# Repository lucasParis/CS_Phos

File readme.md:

Phos
===

USB Serial Protocol for Led Controllers
---
There is one led controller per side of the led pilar.
Each controller is being streamed frames 60 times a second of the leds' brightness by USB serial.
The protocol for the serial transmition consists of a __start byte of 255__ followed by a __list of 3564 bytes of brightness values between 0 and 254__.
These brightness values correspond to each pixel of the strip in series. The strips are arranged in 9 colomns, each with 11 modules of 36pixels long -i.e. 396 leds per colomn.
The data is listed one colomn after the other, starting and the top of the left colomn and making it's way down and then to the next colomn.
Serial baud is 2500000.

Arduino
---
- FastLED version 3.1.6
- Arduino 1.8.2
- Teensyloader 1.26

The best settings to avoid glitches in the apa102 data seems to be:
- teensy clock speed set to 144mhz
- fastled rate 3mhz

Serial baud is 2500000.

The _testCode_ firmware of prototype 2 loops 2 white leds through the strip.

Assembly
---
ribbon cables
power

TouchDesigner patch
---
### prototype 1
Test patch with internally generated patterns and UI to adjust patterns
### prototype 2
streaming patch, with syphon/spout input (to do).
- [ ] add syphon/spout input
- [ ] cleanup UI
- [ ] adapt test patterns from prototype 1
- [ ] add processing example code
- [ ] change total output for only 3 boxes, 1 side

Files
---
- prototype 1
  - Made in september 2018 for tests at the barbican
  - 1 box, 5 strips
- prototype 2
  - Made in October/November 2018
  - 3 boxes, 9 strips, 2 sides
  - custom pcbs version 1, with small changes needed
  - digikey BOMs

BOMs
---

#### BOM_leds_oneBoxSide_digikey

Bill of materials for 1 side of the box, includes power supply and connectors for 6 led breakout pcbs.
2 needed per box.

####  BOM_masterModule_digikey

Bill of materials for master module

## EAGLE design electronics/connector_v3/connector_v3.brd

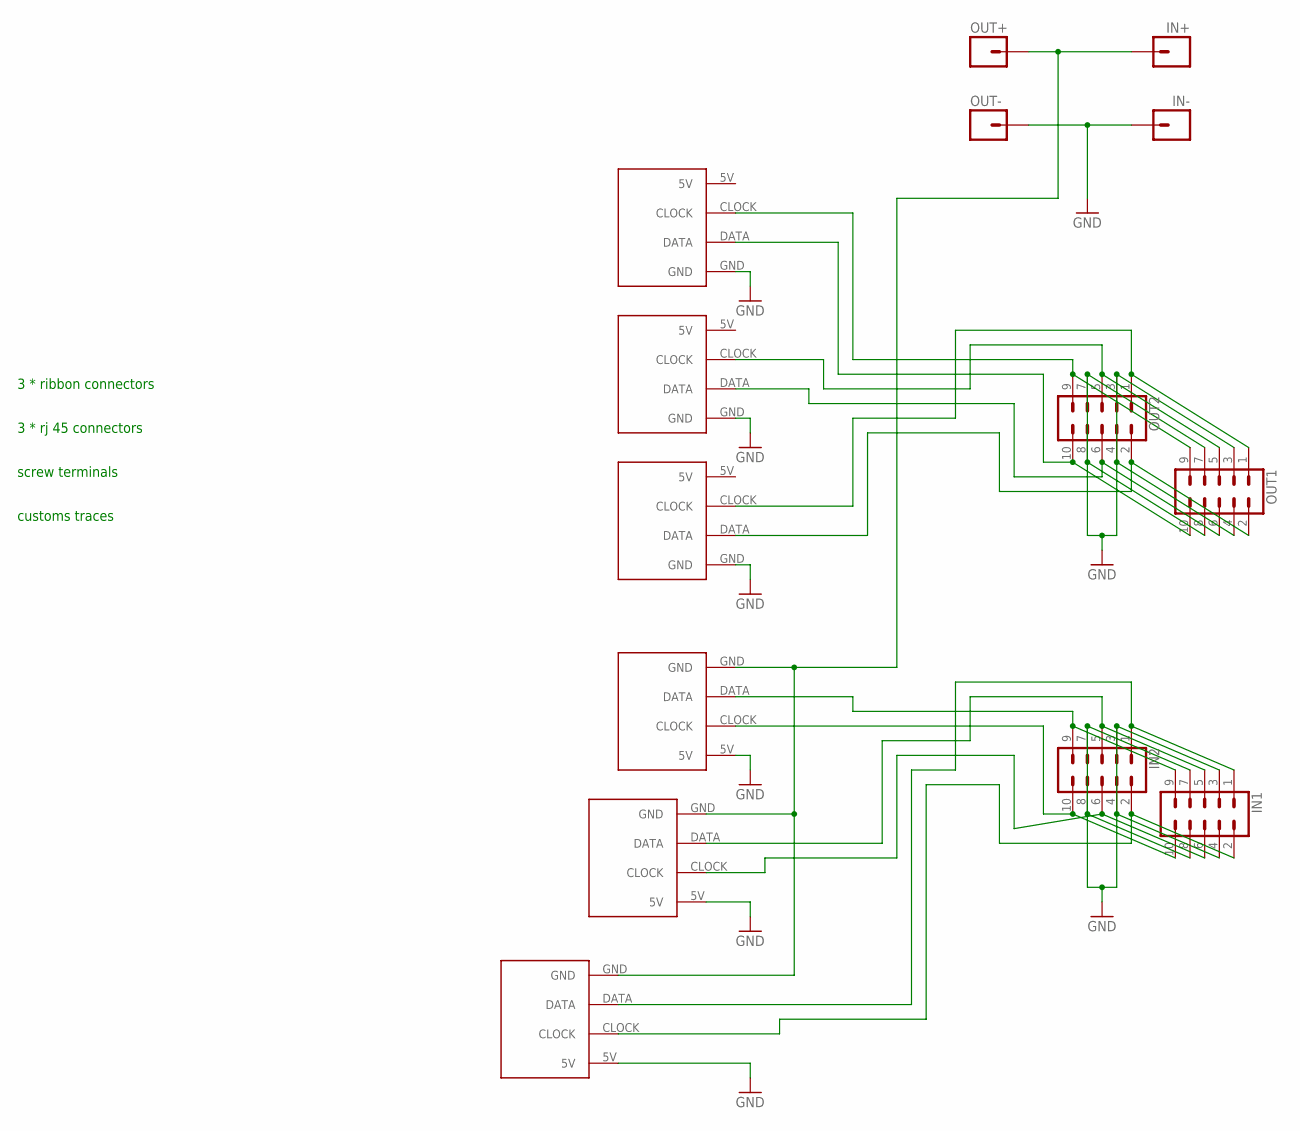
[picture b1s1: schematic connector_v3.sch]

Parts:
IN1, IN2: CONN_05X2SHD_LOCK; 2X5-SHROUDED_LOCK
IN+: M01PTH_2MM; 1X01_2MM
IN-: M01PTH_2MM; 1X01_2MM
INSTRIP1, INSTRIP2, INSTRIP3: APA102STRIP
OUT1, OUT2: CONN_05X2SHD_LOCK; 2X5-SHROUDED_LOCK
OUT+: M01PTH_2MM; 1X01_2MM
OUT-: M01PTH_2MM; 1X01_2MM
OUTSTRIP1, OUTSTRIP2, OUTSTRIP3: APA102STRIP

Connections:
GND: IN1.3, IN1.4, IN1.7, IN1.8, IN2.3, IN2.4, IN2.7, IN2.8, IN-.1, INSTRIP1.5V, INSTRIP2.5V, INSTRIP3.5V, OUT1.3, OUT1.4, OUT1.7, OUT1.8, OUT2.3, OUT2.4, OUT2.7, OUT2.8, OUT-.1, OUTSTRIP1.GND, OUTSTRIP2.GND, OUTSTRIP3.GND
unnamed: IN1.9, IN2.9, INSTRIP3.DATA
unnamed: IN1.10, IN2.10, INSTRIP3.CLOCK
unnamed: IN1.5, IN2.5, INSTRIP2.DATA
unnamed: IN1.6, IN2.6, INSTRIP2.CLOCK
unnamed: IN1.1, IN2.1, INSTRIP1.DATA
unnamed: IN1.2, IN2.2, INSTRIP1.CLOCK
unnamed: IN+.1, INSTRIP1.GND, INSTRIP2.GND, INSTRIP3.GND, OUT+.1
unnamed: OUT1.9, OUT2.9, OUTSTRIP3.CLOCK
unnamed: OUT1.10, OUT2.10, OUTSTRIP3.DATA
unnamed: OUT1.5, OUT2.5, OUTSTRIP2.CLOCK
unnamed: OUT1.6, OUT2.6, OUTSTRIP2.DATA
unnamed: OUT1.1, OUT2.1, OUTSTRIP1.CLOCK
unnamed: OUT1.2, OUT2.2, OUTSTRIP1.DATA

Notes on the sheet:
3 * rj 45 connectors
3 * ribbon connectors
screw terminals
customs traces

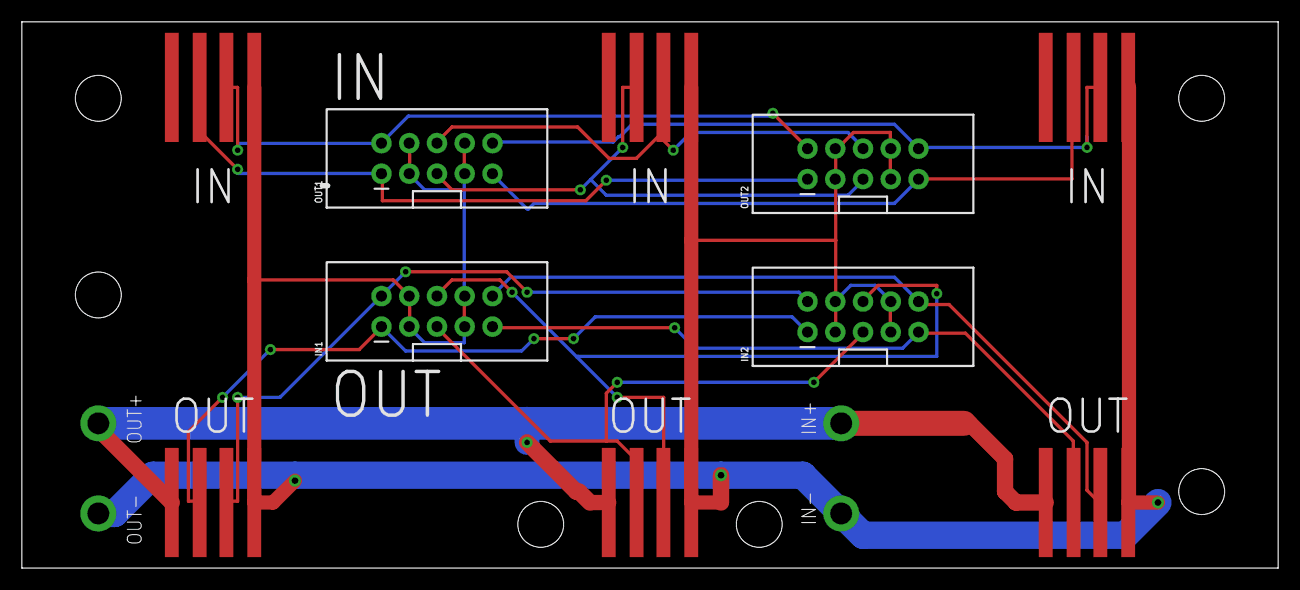
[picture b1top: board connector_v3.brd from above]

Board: 2 copper layers, 115.0 x 50.0 mm, 14 parts (0 on the bottom side), 14 nets.

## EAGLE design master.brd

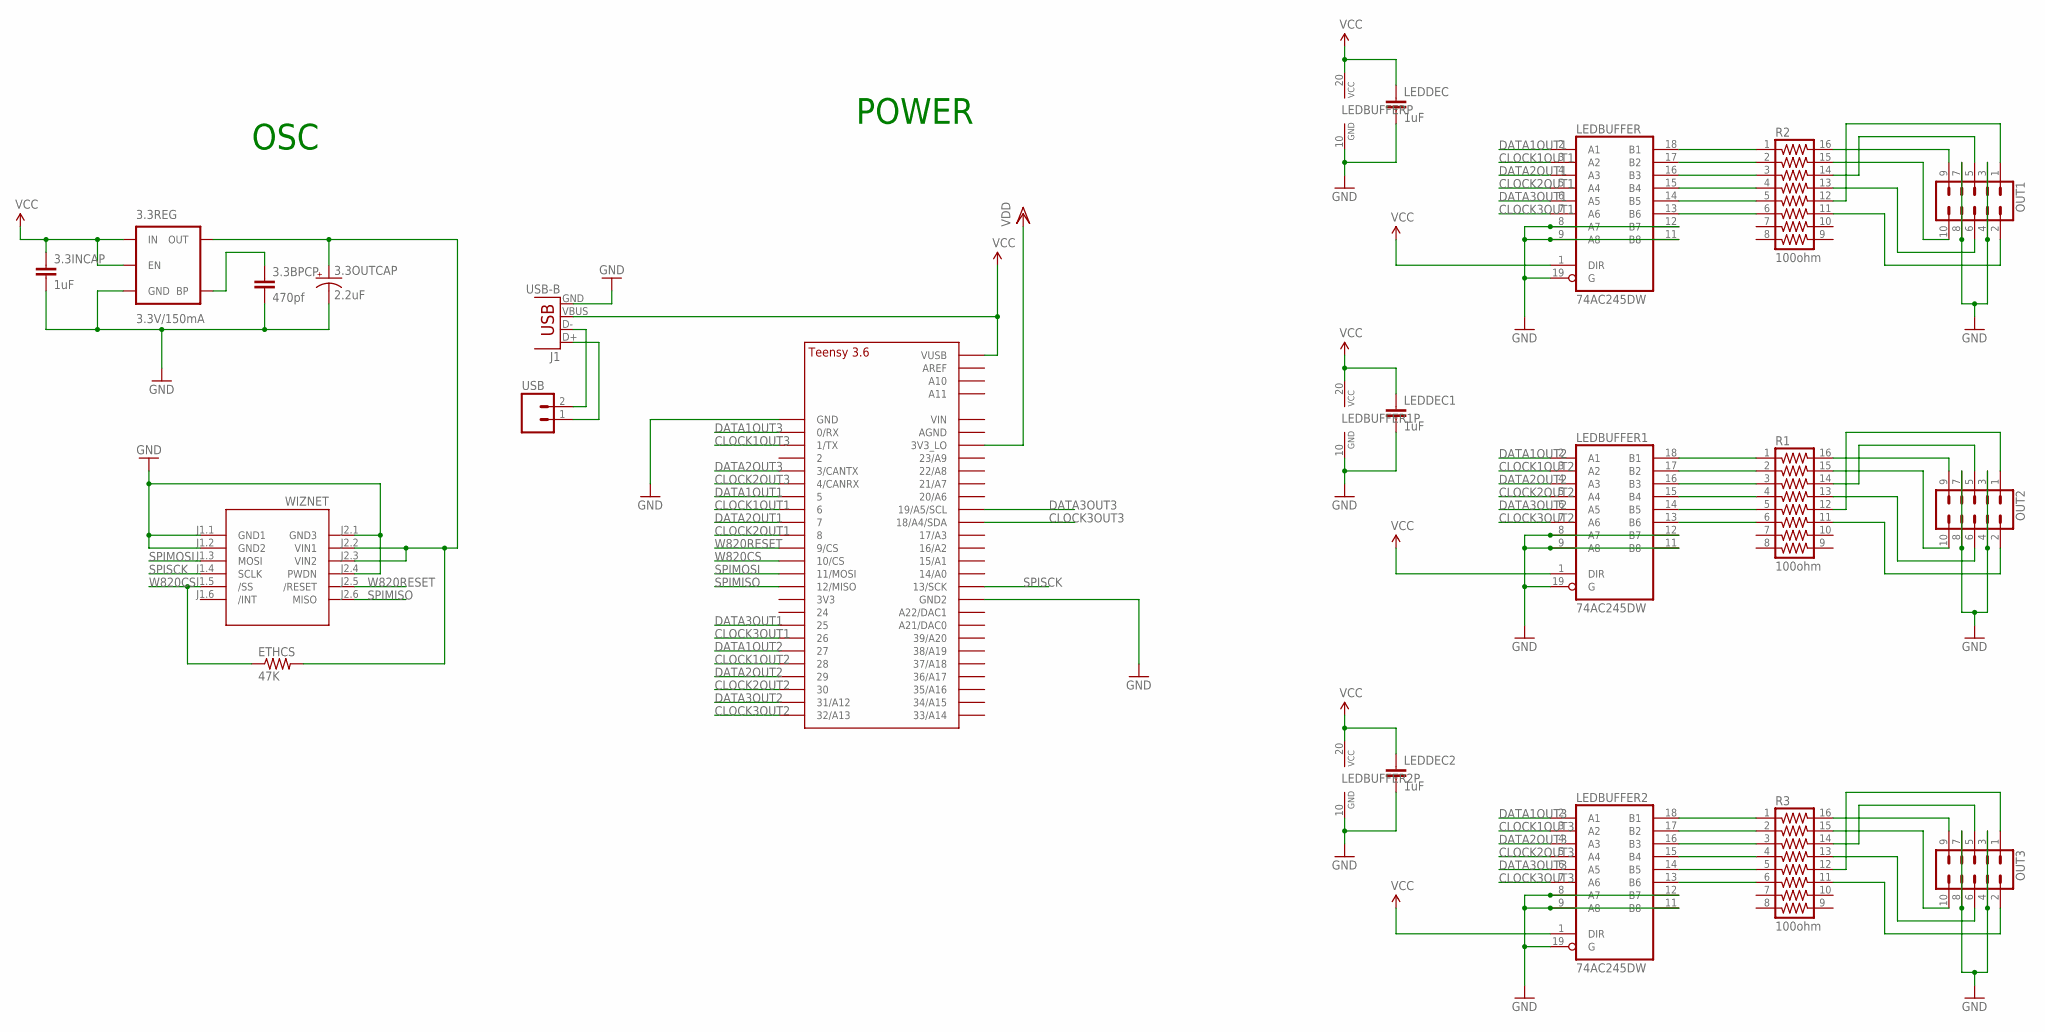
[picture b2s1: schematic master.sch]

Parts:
3.3BPCP: 470pf; 1206
3.3INCAP: 1uF; 1206
3.3OUTCAP: 2.2uF; EIA3528-KIT
3.3REG: 3.3V/150mA; SOT23-5
ETHCS: 47K; 1206
J1: USB-B; USB-B-PTH
LEDBUFFER, LEDBUFFER1, LEDBUFFER2: 74AC245DW; SO20W
LEDDEC, LEDDEC1, LEDDEC2: 1uF; 1206
OUT1, OUT2, OUT3: CONN_05X2SHD_LOCK; 2X5-SHROUDED_LOCK
R1, R2, R3: 100ohm; SO16
U$1: TEENSY_3.5/3.6_BASIC
USB: M02LOCK_LONGPADS; 1X02_LOCK_LONGPADS
WIZNET: WIZ820IO_DEVICE'DUAL-IN-LINE'; WIZ820IO

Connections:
CLOCK1OUT1: LEDBUFFER.3 (A2), U$1.6
CLOCK1OUT2: LEDBUFFER1.3 (A2), U$1.28
CLOCK1OUT3: LEDBUFFER2.3 (A2), U$1.1/TX
CLOCK2OUT1: LEDBUFFER.5 (A4), U$1.8
CLOCK2OUT2: LEDBUFFER1.5 (A4), U$1.30
CLOCK2OUT3: LEDBUFFER2.5 (A4), U$1.4/CANRX
CLOCK3OUT1: LEDBUFFER.7 (A6), U$1.26
CLOCK3OUT2: LEDBUFFER1.7 (A6), U$1.32/A13
CLOCK3OUT3: LEDBUFFER2.7 (A6), U$1.18/A4/SDA
DATA1OUT1: LEDBUFFER.2 (A1), U$1.5
DATA1OUT2: LEDBUFFER1.2 (A1), U$1.27
DATA1OUT3: LEDBUFFER2.2 (A1), U$1.0/RX
DATA2OUT1: LEDBUFFER.4 (A3), U$1.7
DATA2OUT2: LEDBUFFER1.4 (A3), U$1.29
DATA2OUT3: LEDBUFFER2.4 (A3), U$1.3/CANTX
DATA3OUT1: LEDBUFFER.6 (A5), U$1.25
DATA3OUT2: LEDBUFFER1.6 (A5), U$1.31/A12
DATA3OUT3: LEDBUFFER2.6 (A5), U$1.19/A5/SCL
GND: 3.3BPCP.2, 3.3INCAP.2, 3.3OUTCAP.C (-), 3.3REG.2 (GND), J1.GND, LEDBUFFER.8 (A7), LEDBUFFER.9 (A8), LEDBUFFER.10 (GND), LEDBUFFER.11 (B8), LEDBUFFER.12 (B7), LEDBUFFER.19 (G), LEDBUFFER1.8 (A7), LEDBUFFER1.9 (A8), LEDBUFFER1.10 (GND), LEDBUFFER1.11 (B8), LEDBUFFER1.12 (B7), LEDBUFFER1.19 (G), LEDBUFFER2.8 (A7), LEDBUFFER2.9 (A8), LEDBUFFER2.10 (GND), LEDBUFFER2.11 (B8), LEDBUFFER2.12 (B7), LEDBUFFER2.19 (G), LEDDEC.2, LEDDEC1.2, LEDDEC2.2, OUT1.3, OUT1.4, OUT1.7, OUT1.8, OUT2.3, OUT2.4, OUT2.7, OUT2.8, OUT3.3, OUT3.4, OUT3.7, OUT3.8, U$1.GND, U$1.GND2, WIZNET.J1.1 (GND1), WIZNET.J1.2 (GND2), WIZNET.J2.1 (GND3), WIZNET.J2.4 (PWDN)
unnamed: J1.D+, USB.1
unnamed: LEDBUFFER.18 (B1), R2.1
unnamed: LEDBUFFER.17 (B2), R2.2
unnamed: LEDBUFFER.16 (B3), R2.3
unnamed: J1.D-, USB.2
unnamed: LEDBUFFER.15 (B4), R2.4
unnamed: LEDBUFFER.14 (B5), R2.5
unnamed: 3.3OUTCAP.A (+), 3.3REG.5 (OUT), ETHCS.2, WIZNET.J2.2 (VIN1), WIZNET.J2.3 (VIN2)
unnamed: OUT1.9, R2.16
unnamed: OUT1.10, R2.15
unnamed: OUT1.5, R2.14
unnamed: OUT1.6, R2.13
unnamed: OUT1.1, R2.12
unnamed: OUT1.2, R2.11
unnamed: LEDBUFFER1.18 (B1), R1.1
unnamed: LEDBUFFER1.17 (B2), R1.2
unnamed: LEDBUFFER.13 (B6), R2.6
unnamed: LEDBUFFER1.16 (B3), R1.3
unnamed: LEDBUFFER1.15 (B4), R1.4
unnamed: LEDBUFFER1.14 (B5), R1.5
unnamed: LEDBUFFER1.13 (B6), R1.6
unnamed: OUT2.9, R1.16
unnamed: OUT2.10, R1.15
unnamed: OUT2.5, R1.14
unnamed: OUT2.6, R1.13
unnamed: OUT2.1, R1.12
unnamed: OUT2.2, R1.11
unnamed: LEDBUFFER2.18 (B1), R3.1
unnamed: LEDBUFFER2.17 (B2), R3.2
unnamed: LEDBUFFER2.16 (B3), R3.3
unnamed: LEDBUFFER2.15 (B4), R3.4
unnamed: LEDBUFFER2.14 (B5), R3.5
unnamed: LEDBUFFER2.13 (B6), R3.6
unnamed: OUT3.9, R3.16
unnamed: OUT3.10, R3.15
unnamed: OUT3.5, R3.14
unnamed: OUT3.6, R3.13
unnamed: OUT3.1, R3.12
unnamed: OUT3.2, R3.11
unnamed: 3.3BPCP.1, 3.3REG.4 (BP)
SPIMISO: U$1.12/MISO, WIZNET.J2.6 (MISO)
SPIMOSI: U$1.11/MOSI, WIZNET.J1.3 (MOSI)
SPISCK: U$1.13/SCK, WIZNET.J1.4 (SCLK)
VCC: 3.3INCAP.1, 3.3REG.1 (IN), 3.3REG.3 (EN), J1.VBUS, LEDBUFFER.1 (DIR), LEDBUFFER.20 (VCC), LEDBUFFER1.1 (DIR), LEDBUFFER1.20 (VCC), LEDBUFFER2.1 (DIR), LEDBUFFER2.20 (VCC), LEDDEC.1, LEDDEC1.1, LEDDEC2.1, U$1.VUSB
VDD: U$1.3V3_LO
W820CS: ETHCS.1, U$1.10/CS, WIZNET.J1.5 (/SS)
W820RESET: U$1.9/CS, WIZNET.J2.5 (/RESET)

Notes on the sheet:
OSC
POWER

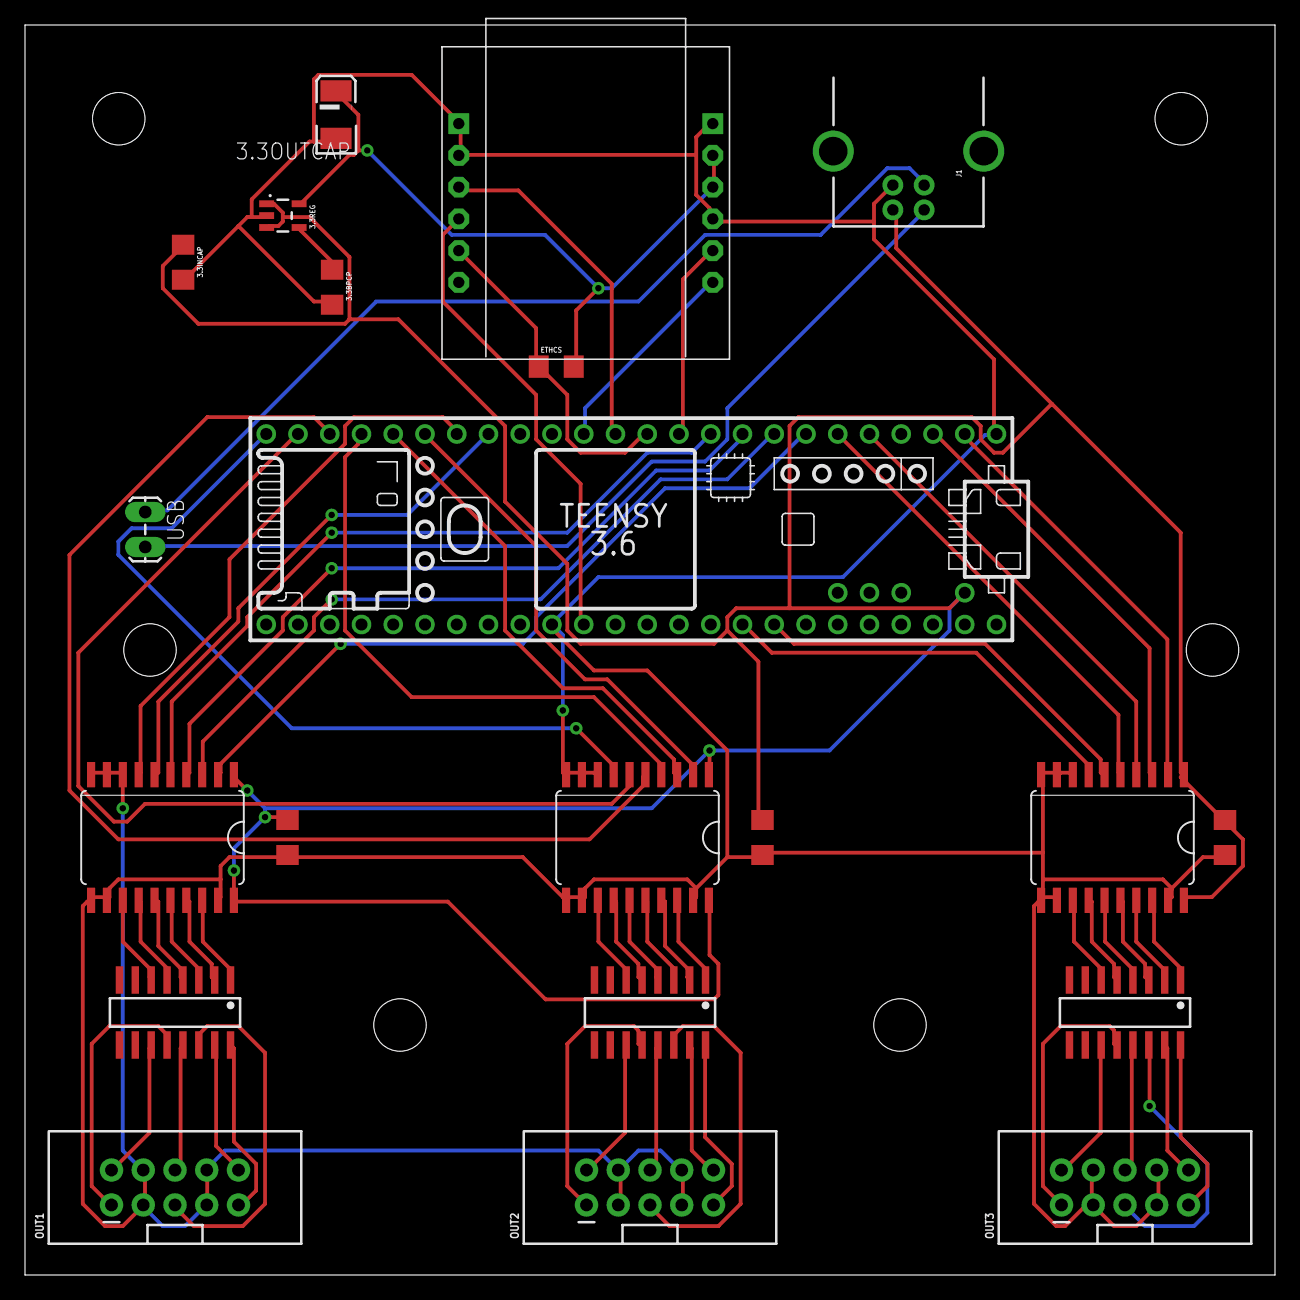
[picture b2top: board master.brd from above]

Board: 2 copper layers, 100.0 x 100.0 mm, 21 parts (0 on the bottom side), 65 nets.

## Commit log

2018-09-24 initial
2018-09-24 added arduino sketch
2018-09-24 removed ds_store
2018-09-24 updated proto
2018-09-24 ignore dsstore
2018-09-24 more dsstore blabla
2018-10-24 added PCB files
2018-10-28 reorganised folders, added readme
2018-10-28 version 2 of connector pcb
2018-11-05 added BOMs
2018-11-05 added BOM readme
2018-11-05 added arduino code for proto 2 and commented code
2018-11-05 added TD patch for proto 2
2018-11-05 updated readme with todo on TD proto2
2019-01-15 connector v3 added mirrored connector to the side
2019-02-13 new pcb version and update TD with processing code
2019-02-14 inverted orientation in Y, changed resolution to 9 * 360 in TD and Processing
2019-02-20 changedSize processing sketch
2020-02-19 updated for udp streaming

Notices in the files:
parts and their libraries:
SparkFun-Connectors: Licensing: Creative Commons ShareAlike 4.0 International - https://creativecommons.org/licenses/by-sa/4.0
